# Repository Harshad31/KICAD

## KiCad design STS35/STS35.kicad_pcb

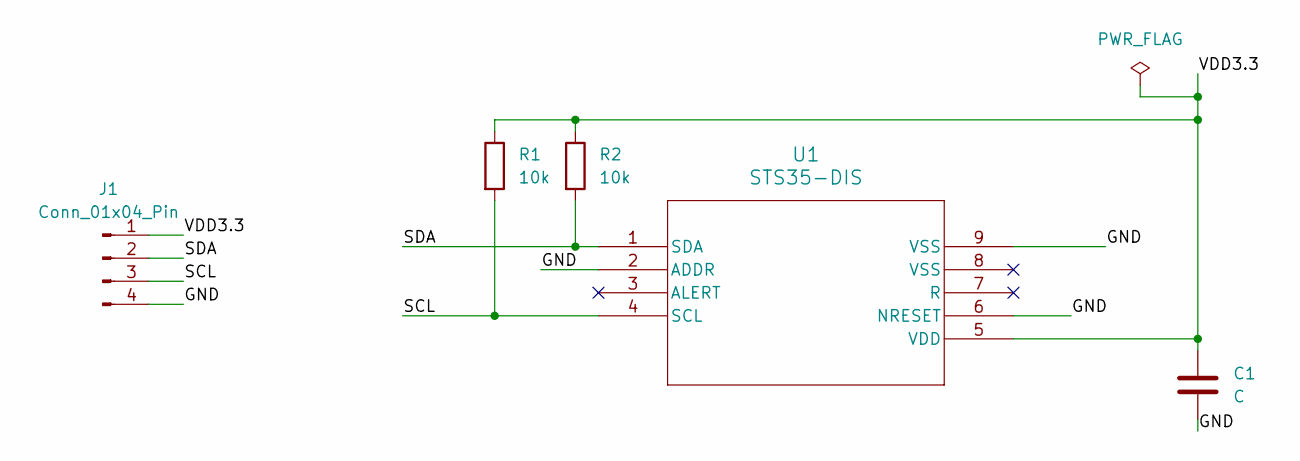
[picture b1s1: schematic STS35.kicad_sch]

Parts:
C1: C; CP_EIA-1608-08_AVX-J
J1: Conn_01x04_Pin; PinSocket_1x04_P2.54mm_Vertical
R1, R2: 10k; R_0201_0603Metric
U1: STS35-DIS; STS3x-DIS_SEN

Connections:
/GND: C1.2, J1.4, U1.2 (ADDR), U1.6 (NRESET), U1.9 (VSS)
/SCL: J1.3, R1.2, U1.4 (SCL)
/SDA: J1.2, R2.2, U1.1 (SDA)
/VDD3.3: C1.1, J1.1, R1.1, R2.1, U1.5 (VDD)

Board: 2 copper layers, 5 parts (0 on the bottom side), 4 nets, no tracks yet.

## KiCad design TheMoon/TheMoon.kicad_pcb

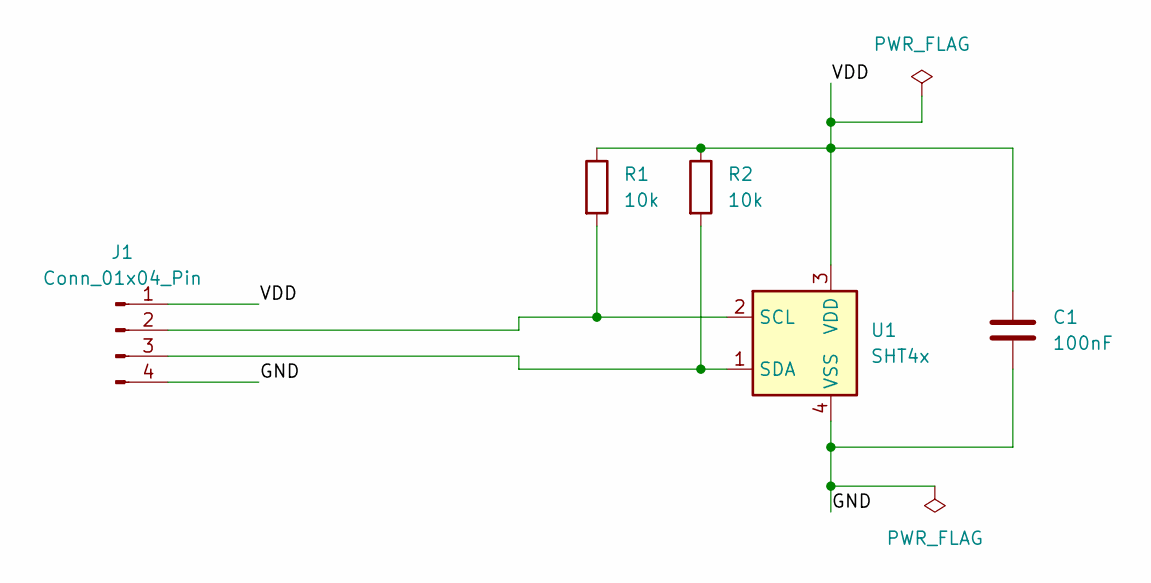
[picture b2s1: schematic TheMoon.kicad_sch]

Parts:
C1: 100nF; CP_EIA-1608-10_AVX-L
J1: Conn_01x04_Pin; PinHeader_1x04_P1.00mm_Vertical
R1, R2: 10k; R_0201_0603Metric
U1: SHT4x; Sensirion_DFN-4_1.5x1.5mm_P0.8mm_SHT4x_NoCentralPad

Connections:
/GND: C1.2, J1.4, U1.4 (VSS)
/VDD: C1.1, J1.1, R1.1, R2.1, U1.3 (VDD)
unnamed: J1.2, R1.2, U1.2 (SCL)
unnamed: J1.3, R2.2, U1.1 (SDA)

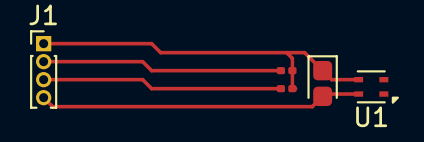
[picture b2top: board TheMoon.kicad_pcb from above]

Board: 2 copper layers, 5 parts (0 on the bottom side), 4 nets.
